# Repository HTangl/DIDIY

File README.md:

# DIDIY #  

The DIDIY is an all in one board designed to make building a rectangle controller much more simple and straightforward.  

If you’d like to assemble one of these boards yourself this repository contains the files necessary to order the boards from JLCPCB. They have a 5 board minimum order but the boards are pretty cheap.  

## How to order from JLCPCB ##  

1. Download the files in this repo by clicking on the green code button in the top right corner and then click on “Download ZIP”. Unzip the folder and grab the gerber zip file from the fabrication folder. Do not unzip the gerber zip file.  

2. Go to https://jlcpcb.com/ and click “Order now” at the top right. Click on the blue “Add gerber file” button and upload the gerber zip file.  

3. You can leave all of the options set to default. Only thing you might want to change is the pcb color, this doesn’t add cost but it does increase production time. All you have to do now is click “SAVE TO CART” on the right and finish the checkout process. I recommend using DHL shipping, it’s expensive but has proven to be very reliable.  

## Other parts needed for assembly ##  

1 - [Raspberry Pi Pico](https://www.pishop.us/product/raspberry-pi-pico/)  
1 - Model UD, these can also be ordered from JLCPCB, there’s an ordering guide on the [Model UD github page](https://github.com/HTangl/Model-UD). The Model UD isn't absolutely required, you can instead simply hard wire a USB or GC cable to the USB/GC pin bank on the right, there are 2 holes at the top right that can be used to zip tie the cable in place as well.  
9 - [3 pin 3.5mm pitch screw terminal](https://amazon.com/dp/B07B79Q911)  
1 - [2 pin 3.5mm pitch screw terminal](https://amazon.com/dp/B07B791NMQ)   
1 – Set of [2.54 pitch male pin headers](https://amazon.com/dp/B07PKKY8BX)  

## Assembly guide ##  

Before soldering anything you should test your Pico by uploading firmware onto it, I recommend using the [Htangl Firmware](https://github.com/HTangl/HTangl-Firmware).  
Here is a guide on how to get the DIDIY set up on Slippi and Wii/Switch after you have completed the build - https://www.htangl.com/didiy-guide  
Although both HayBox and Pico Rectangle can be used on the DIDIY you will have to change the pinout file if you intend to use either of them.  

1. Start by soldering the Pico USB data pads to the DIDIY. These are the 2 small pads underneath the usb port labeled as TP2 and TP3. Add a small amount of solder to both of the pads as well as the correlating through holes on the DIDIY.  

2. You will now need to align the Pico to the DIDIY board, I use a breadboard to do this but it’s not required. You can just stick pin headers through the top of the Pico and then through the didiy and flip the boards over together. Now press the DIDIY down into the Pico and heat up the through holes that connect to the data pads. You are trying to melt the solder on the Pico pads so that it fuses to the through holes on the DIDIY. I usually hold my iron on each hole for about 2-3 seconds and alternate between them a few times.  

3. Remove the pin headers and flip the board over. The Pico should be flat against the DIDIY, if it isn’t re insert the pin headers and try heating up the through holes a little longer. It’s a good idea to now check to see if the pads on the Pico are properly connected to the DIDIY. To do this you’ll need a multi meter with a continuity test mode. Test between the tiny pins on the back of the Pico USB and the D+/D- pins on the DIDIY (you can use either set of data pins on the DIDIY). If you have continuity on both pins you’re good to go and you can move on to the next step. If not try repeating step 2.  

4. Next solder all the pins on the Pico. I recommend soldering any 2 pins on opposite sides near the back side of the Pico furthest from the micro usb port. The back end can sometimes stick up a little bit even if you soldered the data pins properly so it helps to solder pins at the back while pressing the Pico down to make sure it’s perfectly flat against the DIDIY.  

5. Now solder the Model UD to the DIDIY. Start by inserting 2 rows of 4 pin headers with the short side facing towards the top of the board, the plastic spacers should be on the top side. You can either solder the pins to the DIDIY then put the Model UD on and solder it to the pins or vice versa. I usually solder the pins to the DIDIY first but do whatever is easiest for you, just make sure the Model UD is mounted with the USB port facing down and be careful not to tilt it while soldering. The pins should poke through the Model UD holes an even amount on both sides.  

6. Last step is to solder all the screw terminals on. Start by attaching 7 of the 3 pin terminals together, they can be a little tricky to slide together so make sure they’re flush to each other. Now attach another 2 3 pin terminals together for the USB/GC pin bank, if you aren’t going to hardwire a GC or USB cable you do not need to install these terminals. Insert all of the terminals into the board and solder them in place, the picture doesn’t show the 2 pin terminal but it’s used for the Select/Home buttons. Also note that I face the USB/GC and Select/Home terminals inwards towards the middle of the DIDIY. This is in an effort to keep wires from running out the sides of the board but is purely a preference thing, you can face them outwards if you like.  

7. All that’s left now is snipping off the excess pins sticking out the back of the board. Use a pair of flush cutters to cut them. The pins like to go flying off when cut so I line up the cutters then put a towel over top of the board and then snip one pin. Repeat until all the pins are flush.  

### - License - ###  

This repository is licensed under the CERN Open Hardware Licence Version 2 - Strongly Reciprocal. Please read the license in this repository and visit https://ohwr.org/cernohl for more information. This license allows you to make a modified or unmodified version of the board for yourself or to sell provided you follow the guidelines of the license. The strongly reciprocal version of the license I have chosen requires that you use this same license if you decide to make modifications to any of the files in this repository.

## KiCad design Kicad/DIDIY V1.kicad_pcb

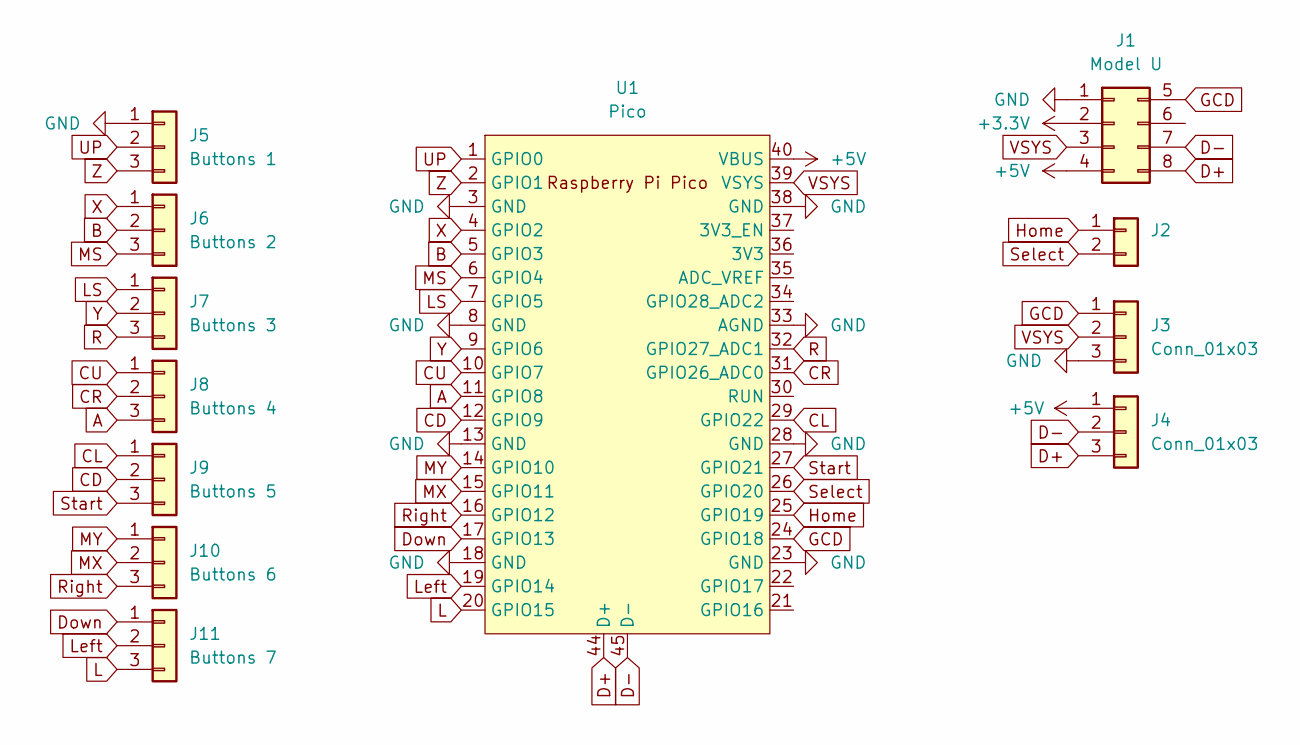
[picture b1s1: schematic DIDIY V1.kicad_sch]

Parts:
J1: Model U; Model_UD_Header
J2: Conn_01x02; Degson_DG350_1X02_Screw_Terminal
J3, J4: Conn_01x03; Degson_DG350_1X03_Screw_Terminal
J5: Buttons 1; Degson_DG350_1X03_Screw_Terminal
J6: Buttons 2; Degson_DG350_1X03_Screw_Terminal
J7: Buttons 3; Degson_DG350_1X03_Screw_Terminal
J8: Buttons 4; Degson_DG350_1X03_Screw_Terminal
J9: Buttons 5; Degson_DG350_1X03_Screw_Terminal
J10: Buttons 6; Degson_DG350_1X03_Screw_Terminal
J11: Buttons 7; Degson_DG350_1X03_Screw_Terminal
U1: Pico; RPi_Pico_Removed3Pins

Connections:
+3V3: J1.2
+5V: J1.4, J4.1, U1.40 (VBUS)
A: J8.3, U1.11 (GPIO8)
B: J6.2, U1.5 (GPIO3)
CD: J9.2, U1.12 (GPIO9)
CL: J9.1, U1.29 (GPIO22)
CR: J8.2, U1.31 (GPIO26_ADC0)
CU: J8.1, U1.10 (GPIO7)
D+: J1.8, J4.3, U1.44 (D+)
D-: J1.7, J4.2, U1.45 (D-)
Down: J11.1, U1.17 (GPIO13)
GCD: J1.5, J3.1, U1.24 (GPIO18)
GND: J1.1, J3.3, J5.1, U1.3 (GND), U1.8 (GND), U1.13 (GND), U1.18 (GND), U1.23 (GND), U1.28 (GND), U1.33 (AGND), U1.38 (GND)
Home: J2.1, U1.25 (GPIO19)
L: J11.3, U1.20 (GPIO15)
LS: J7.1, U1.7 (GPIO5)
Left: J11.2, U1.19 (GPIO14)
MS: J6.3, U1.6 (GPIO4)
MX: J10.2, U1.15 (GPIO11)
MY: J10.1, U1.14 (GPIO10)
R: J7.3, U1.32 (GPIO27_ADC1)
Right: J10.3, U1.16 (GPIO12)
Select: J2.2, U1.26 (GPIO20)
Start: J9.3, U1.27 (GPIO21)
UP: J5.2, U1.1 (GPIO0)
VSYS: J1.3, J3.2, U1.39 (VSYS)
X: J6.1, U1.4 (GPIO2)
Y: J7.2, U1.9 (GPIO6)
Z: J5.3, U1.2 (GPIO1)

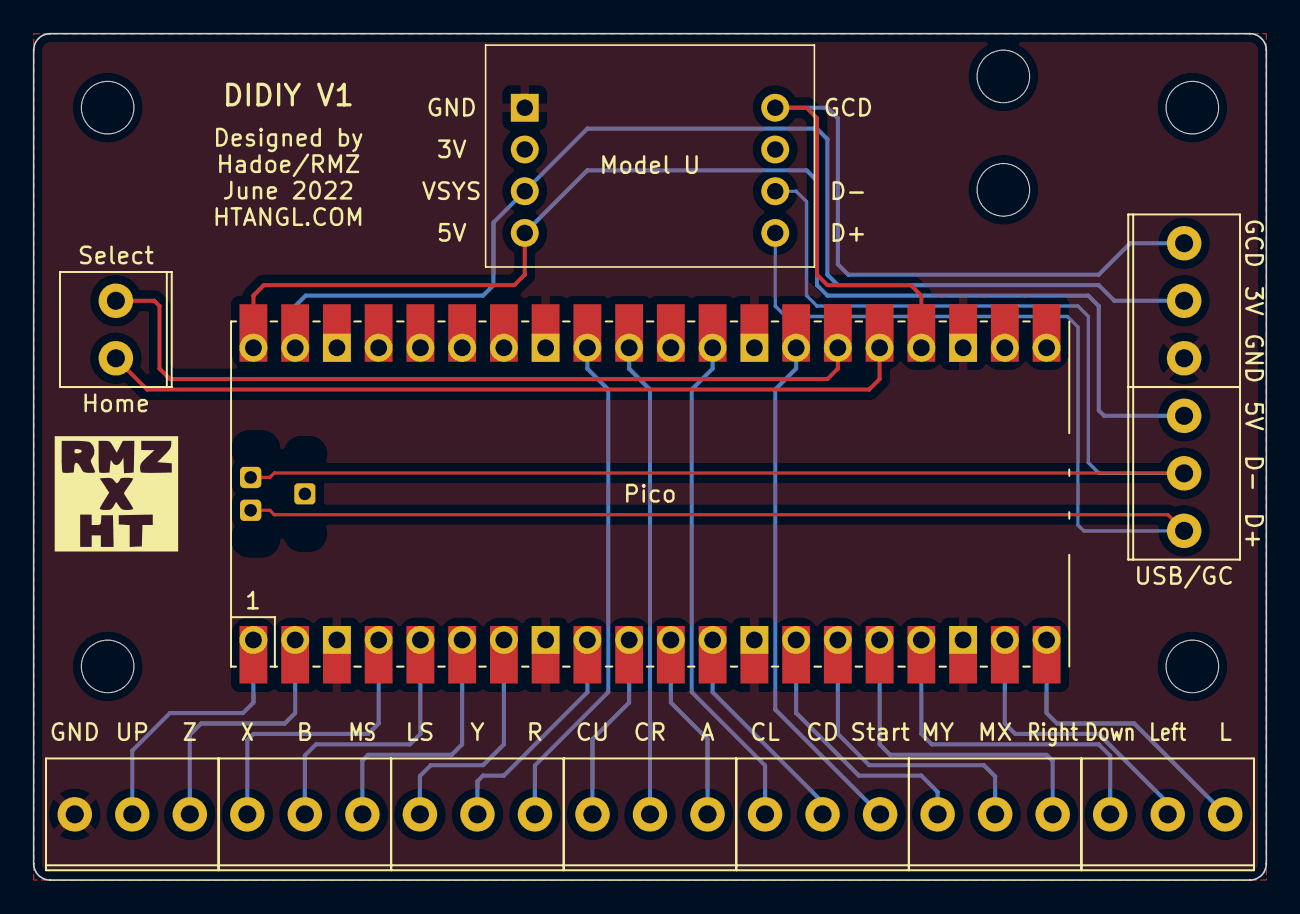
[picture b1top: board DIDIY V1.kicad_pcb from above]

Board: 2 copper layers, 75.0 x 51.5 mm, 12 parts (1 on the bottom side), 28 nets.
